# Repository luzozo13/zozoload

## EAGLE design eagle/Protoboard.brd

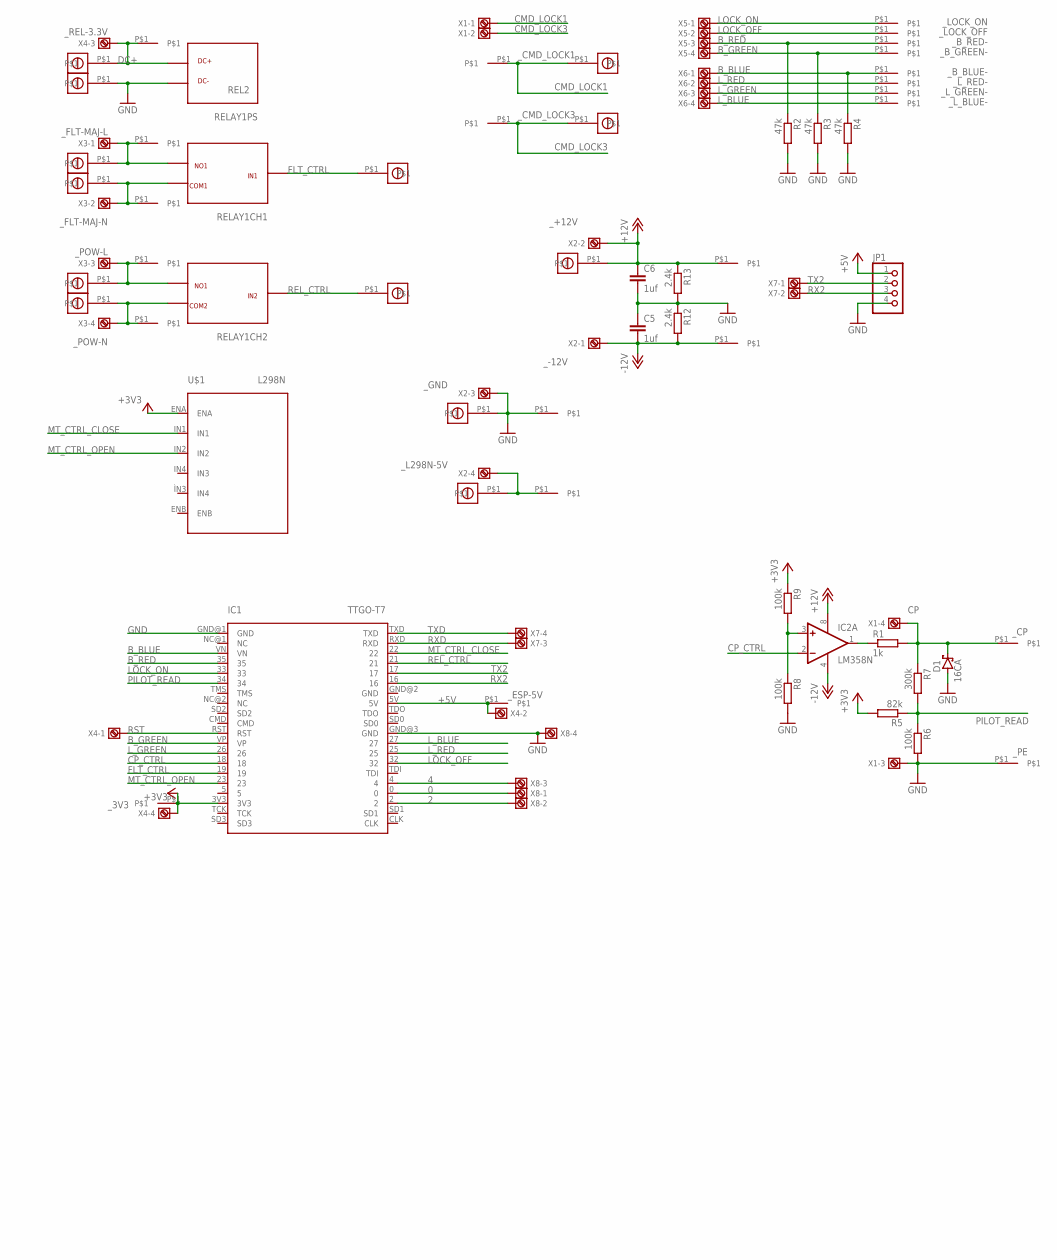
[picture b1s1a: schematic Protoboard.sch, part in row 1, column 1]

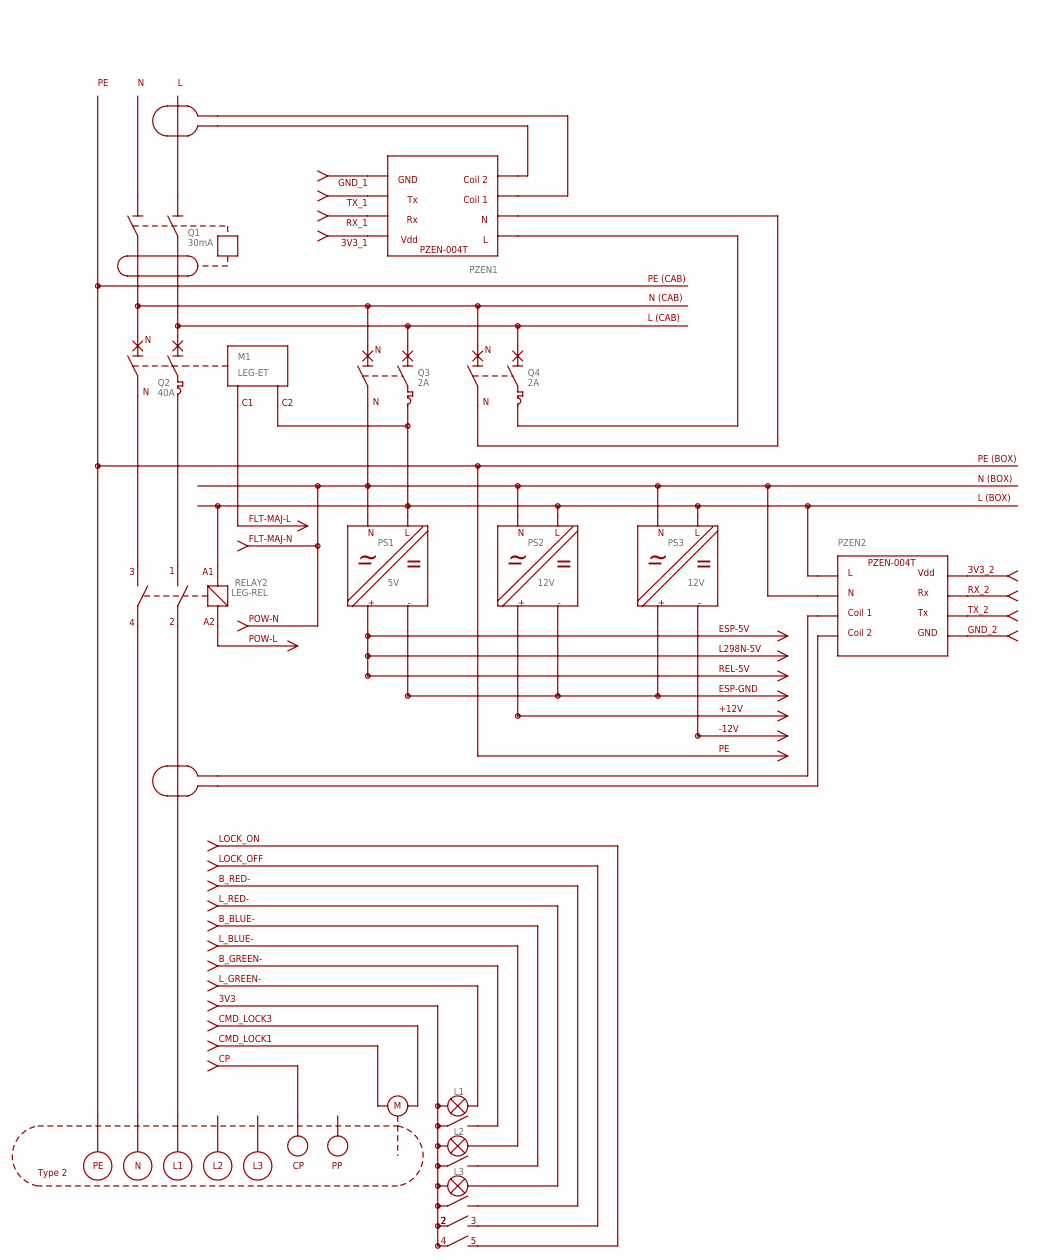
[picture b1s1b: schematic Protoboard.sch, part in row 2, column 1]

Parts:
5V, 12V: BORNIER
C5, C6: 1uf; C050-025X075
D1: 16CA; C1702-15
DC+: BORNIER
DC-: BORNIER
FLT-L: BORNIER
FLT-N: BORNIER
GND: BORNIER
IC1: TTGO-T7
IC2: LM358N; DIL08
IN1, IN2: BORNIER
JP1: PINHD-1X4; 1X04
MT1, MT2: BORNIER
POW-L: BORNIER
POW-N: BORNIER
R1: 1k; 0207/10
R2, R3, R4: 47k; 0207/10
R5: 82k; 0207/10
R6, R8, R9: 100k; 0207/10
R7: 300k; 0207/10
R12, R13: 2.4k; 0207/10
RELAY1: REL2
U$1: L298N
X1, X2, X3, X4, X5, X6, X7, X8: 1727036
_3V3: PIN
_+12V: PIN
_-12V: PIN
_B_BLUE-: PIN
_B_GREEN-: PIN
_B_RED-: PIN
_CMD_LOCK1, _CMD_LOCK3: PIN
_CP: PIN
_ESP-5V: PIN
_FLT-MAJ-L: PIN
_FLT-MAJ-N: PIN
_GND: PIN
_L298N-5V: PIN
_LOCK_OFF: PIN
_LOCK_ON: PIN
_L_BLUE-: PIN
_L_GREEN-: PIN
_L_RED-: PIN
_PE: PIN
_POW-L: PIN
_POW-N: PIN
_REL-3.3V: PIN

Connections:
0: IC1.0, X8.1
2: IC1.2, X8.2
4: IC1.4, X8.3
+3V3: IC1.3V3, R5.2, R9.1, U$1.ENA, X4.4, _3V3.P$1
+5V: IC1.5V, JP1.1, X4.2, _ESP-5V.P$1
+12V: 12V.P$1, C6.1, IC2.8 (V+), R13.1, X2.2, _+12V.P$1
-12V: C5.2, IC2.4 (V-), R12.2, X2.1, _-12V.P$1
B_BLUE: IC1.VN, R4.1, X6.1, _B_BLUE-.P$1
B_GREEN: IC1.VP, R3.1, X5.4, _B_GREEN-.P$1
B_RED: IC1.35, R2.1, X5.3, _B_RED-.P$1
CMD_LOCK1: MT2.P$1, X1.2, _CMD_LOCK1.P$1
CMD_LOCK3: MT1.P$1, X1.1, _CMD_LOCK3.P$1
CP: D1.C, R1.2, R7.1, X1.4, _CP.P$1
CP_CTRL: IC1.18, IC2.2 (-IN)
DC+: DC+.P$1, X4.3, _REL-3.3V.P$1
FLT_CTRL: IC1.19, IN1.P$1
GND: C5.1, C6.2, D1.A, DC-.P$1, GND.P$1, IC1.GND@1 (GND), IC1.GND@3 (GND), JP1.4, R2.2, R3.2, R4.2, R6.2, R8.2, R12.1, R13.2, X1.3, X2.3, X8.4, _GND.P$1, _PE.P$1
LOCK_OFF: IC1.32, X5.2, _LOCK_OFF.P$1
LOCK_ON: IC1.33, X5.1, _LOCK_ON.P$1
L_BLUE: IC1.27, X6.4, _L_BLUE-.P$1
L_GREEN: IC1.26, X6.3, _L_GREEN-.P$1
L_RED: IC1.25, X6.2, _L_RED-.P$1
MT_CTRL_CLOSE: IC1.22, U$1.IN1
MT_CTRL_OPEN: IC1.23, U$1.IN2
unnamed: FLT-N.P$1, X3.2, _FLT-MAJ-N.P$1
unnamed: FLT-L.P$1, X3.1, _FLT-MAJ-L.P$1
unnamed: IC2.1 (OUT), R1.1
unnamed: POW-L.P$1, X3.3, _POW-L.P$1
unnamed: POW-N.P$1, X3.4, _POW-N.P$1
unnamed: IC2.3 (+IN), R8.1, R9.2
unnamed: 5V.P$1, X2.4, _L298N-5V.P$1
PILOT_READ: IC1.34, R5.1, R6.1, R7.2
REL_CTRL: IC1.21, IN2.P$1
RST: IC1.RST, X4.1
RX2: IC1.16, JP1.3, X7.2
RXD: IC1.RXD, X7.3
TX2: IC1.17, JP1.2, X7.1
TXD: IC1.TXD, X7.4

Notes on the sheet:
PE (CAB)
N (CAB)
L (CAB)
PE (BOX)
N (BOX)
L (BOX)
REL-5V
ESP-GND
+12V
-12V
FLT-MAJ-L
FLT-MAJ-N
POW-N
POW-L
CMD_LOCK1
CMD_LOCK3
3V3
L_GREEN-
L_BLUE-
L_RED-
LOCK_OFF
LOCK_ON
L298N-5V
ESP-5V
B_RED-
B_BLUE-
B_GREEN-
GND_2
TX_2
RX_2
3V3_2
GND_1
TX_1
RX_1
3V3_1

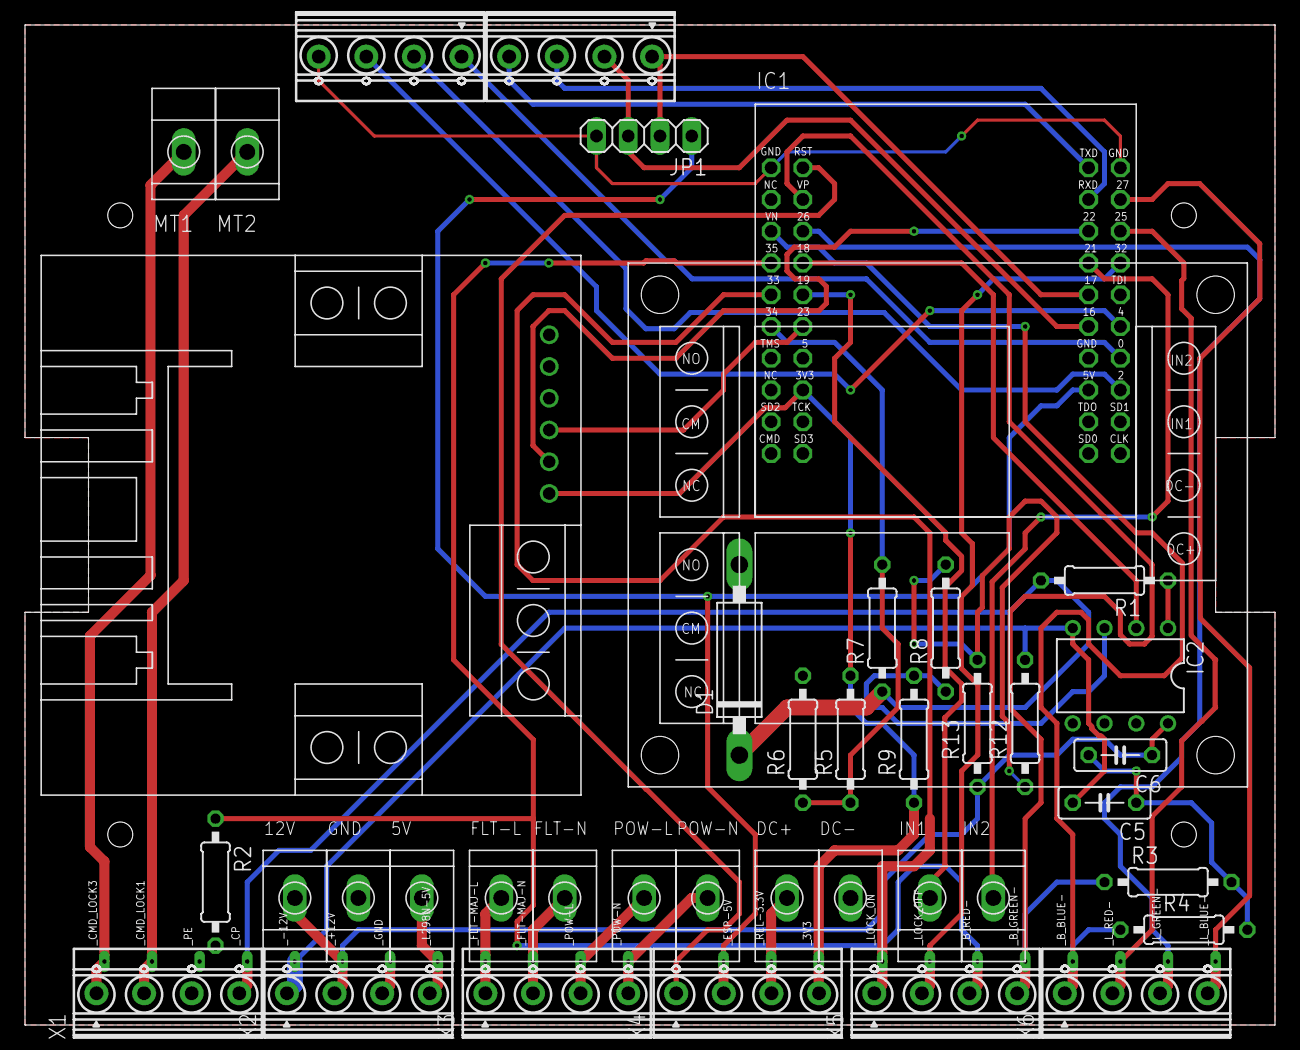
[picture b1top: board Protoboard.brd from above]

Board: 2 copper layers, 100.0 x 80.0 mm, 63 parts (0 on the bottom side), 38 nets.

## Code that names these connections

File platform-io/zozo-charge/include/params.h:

#pragma once

#include <Arduino.h>  // For byte type definition

// Forward declarations
class MqttHandler;
class PZEM004Tv30; // PZEM type forward declaration

//-- Pin Assignments --//
// EV Charger Control Pins
#define CP_CTRL 18          // Control Pilot PWM output
#define FLT_CTRL 19         // Fault control output
#define REL_CTRL 21         // Main relay control
#define MT_CTRL_CLOSE 22    // Motor control - close
#define MT_CTRL_OPEN 23     // Motor control - open

// LED Pins  
#define L_R 25              // Red LED
#define L_G 26              // Green LED
#define L_B 27              // Blue LED

// Lock Control Pins
#define LOCK_ON 32          // Lock engage input
#define LOCK_OFF 33         // Lock disengage input

// Input Pins
#define PILOT_READ 34       // Control Pilot voltage reading (analog)
#define B_R 35              // Red button input
#define B_G 36              // Green button input  
#define B_B 39              // Blue button input

//-- PZEM Current Measurement --//
#define PZEM_RX_PIN 3      // PZEM RX pin (connect to PZEM TX)
#define PZEM_TX_PIN 1      // PZEM TX pin (connect to PZEM RX)
#define PZEM_ADDR 0x04      // PZEM device address
#define PZEM_UPDATE_INTERVAL 5000  // Update every 5 seconds
#define PZEM_TEST_MODE 0    // Set to 1 for simulated readings, 0 for real hardware

//-- PWM Configuration --//
#define CH_CP_CTRL 0        // PWM channel for Control Pilot
#define F_PWM 1000          // PWM frequency in Hz (1kHz)
#define PWM_RES 8           // PWM resolution in bits (8-bit: 0-255)

//-- EVSE State Definitions --//
#define STATE_INIT 0
#define STATE_A 1           // Vehicle not connected
#define STATE_B 2           // Vehicle connected, not ready
#define STATE_C 3           // Vehicle connected and ready/charging
#define STATE_SLEEPING 4    // CP set to +12V, waiting before opening relay (J1772 stop sequence)
#define STATE_FAULT -1      // Fault state

#define SLEEP_RELAY_OPEN_TIMEOUT_MS 3000  // Max ms to wait for EV to release before forcing relay open

//-- CP Fault Detection (state D/E: CP below TH_CD, e.g. CP shorted to ground) --//
// 0 = report only: a steady low CP is published as a "cp_fault_seen" event on
//     state/change, but the state machine ignores it (previous behaviour).
// 1 = enforce: a steady low CP goes to STATE_FAULT (relay open, FLT_CTRL high).
// Run with 0 first and check no event shows up during normal charging.
#define FAULT_DETECT_ENFORCE 0
#define FAULT_RETRY_MS       30000  // Min time held in STATE_FAULT before it may clear

//-- Debug Flags (bitmask — each flag gates its corresponding state topic) --//
#define DBG_DETAILS  0x01   // state/details  (EVSE state periodic)
#define DBG_CHANGE   0x02   // state/change   (EVSE state transitions)
#define DBG_PZEM     0x04   // state/pzem     (power meter telemetry)
#define DBG_COMM     0x08   // state/comm     (connection status)
#define DBG_TIME     0x10   // state/time     (NTP / uptime)

//-- NVS Persistence --//
// Bump NVS_SCHEMA_VERSION to force-reset all NVS settings on next upload
#define NVS_SCHEMA_VERSION  5
#define DBG_DEFAULT_FLAGS   0x1F  // All 5 flags on by default

//-- Power model: car draw vs CP PWM --//
// Measured, linear between POWER_MODEL_PWM_MIN and POWER_MODEL_PWM_MAX:
//   W = POWER_MODEL_W_AT_PWM0 - POWER_MODEL_W_PER_PWM * pwm
// Outside that range the car saturates (its own max current below, its 6A floor
// above). tools/pwm_sweep.py fits these after a sweep and prints the lines to
// paste here (also in the ESPHome port: evse_params.h). Used by set/power_w and
// by the solar jump. Values: sweep of 2026-09-28 (fit over 110-215, worst error
// 178 W); 105 set by hand, where the car stops taking more (7.27 kW, 31 A).
#define POWER_MODEL_W_AT_PWM0  13723.7f  // W, intercept of the fit
#define POWER_MODEL_W_PER_PWM  59.01f    // W less per PWM step
#define POWER_MODEL_PWM_MIN    105       // Most current the car takes (lower PWM: no gain)
#define POWER_MODEL_PWM_MAX    215       // Least current (car's 6A floor)

//-- Solar Tracking Mode --//
// Closed-loop control: every SOLAR_LOOP_MS, compare the energy planner's setpoint
// (MQTT_EVSE_SETPOINT: solar production minus the other loads) vs EVSE
// consumption (PZEM). Outside the deadband, jump straight to the power model's
// PWM for the setpoint (SOLAR_JUMP), or step when the model points the wrong way
// (other car): surplus -> decrement PWM (more current), deficit -> increment PWM
// (less current). PWM clamped to [SOLAR_PWM_MIN, SOLAR_PWM_MAX].
#define SOLAR_JUMP        1     // 0: fixed steps only (no power model)
#define SOLAR_PWM_MIN     POWER_MODEL_PWM_MIN  // Max charging current (lowest PWM duty)
#define SOLAR_PWM_MAX     POWER_MODEL_PWM_MAX  // Min charging current
// Deadband: above the power model's worst error (~210 W) and the setpoint's 10 s
// jitter (p95 ~190 W, 2026-09 HA history), so the loop holds on noise. Each step
// stays below the deadband (x ~59 W/PWM): a step can never overshoot past it.
#define SOLAR_DEADBAND_W  250   // No change when |setpoint - evse_power| <= this
#define SOLAR_STEP_DOWN   3     // PWM decrement step (more current, ~175 W) on surplus
#define SOLAR_STEP_UP     5     // PWM increment step (less current, ~290 W) on deficit
#define SOLAR_LOOP_MS     10000 // Control loop period (ms)
// Setpoint freshness: the energy planner publishes at least every 30 s, and stops
// when the solar meter is silent. With no setpoint message for this long, the loop stops trusting
// the last value and falls back to minimum current (SOLAR_PWM_MAX) until data
// comes back, instead of charging from the grid on a stale surplus.
#define SOLAR_STALE_MS    180000
// Solar pause/resume (anti-flicker): when already at minimum current and still
// in deficit (or setpoint stale), pause charging instead of drawing from the
// grid. Minimum on/off times keep the contactor from cycling on unsteady sun.
#define SOLAR_PAUSE_AFTER_MS   600000   // Deficit at min current this long -> pause
#define SOLAR_MIN_ON_MS        900000   // Never pause sooner than this after charging (re)started
#define SOLAR_MIN_PAUSE_MS    1200000   // Once paused, stay paused at least this long
#define SOLAR_RESUME_W           2300   // Setpoint needed to resume (~8A x 230V + margin)
#define SOLAR_RESUME_AFTER_MS  600000   // Setpoint >= SOLAR_RESUME_W this long -> resume

//-- Unified config NVS defaults --//
#define NVS_DEFAULT_HOSTNAME      "zozo-charge"
#define NVS_DEFAULT_PZEM_ADDR     0x04
#define NVS_DEFAULT_PZEM_ACQ_RATE 5     // seconds
#define NVS_DEFAULT_PZEM_PUB_RATE 30    // seconds (state/pzem publish interval)

//-- Control Pilot Thresholds (ADC values) --//
// Based on J1772 specification voltage levels
#define TH_AB 3770          // Threshold between State A and B (~11V)
#define TH_BC 3135          // Threshold between State B and C (~9V)  
#define TH_CD 2400          // Threshold between State C and D (~6V)

//-- Control Pilot PWM Values --//
// J1772 compliant PWM duty cycles for current encoding
#define CP_AMP_8 221        // 8A charging current
#define CP_AMP_16 187       // 16A charging current
#define CP_AMP_BOOST 170    // Higher current (boost mode)
#define CP_12P 0            // +12V steady state (State A)
#define CP_12N 255          // -12V steady state (fault condition)

//-- Timing Constants --//
// OpenEVSE-style debouncing delays
#define DELAY_STATE_TRANSITION 250    // Standard state transition debounce (ms)
#define DELAY_STATE_TRANSITION_A 25   // Faster debounce for State A (ms)

// Publishing and communication intervals
#define UL_STATE_PUBLISH_INTERVAL 10000  // State publishing interval (ms)
#define MQTT_RECONNECT_INTERVAL   10000  // Min ms between MQTT reconnect attempts (non-blocking)
#define WIFI_CONNECT_TIMEOUT_MS   20000  // Max wait for WiFi in setup(), then continue offline
#define WDT_TIMEOUT_S             10     // Task watchdog: reboot (relay opens) if loop() hangs

// Legacy timing (for compatibility)
#define STATE_CHANGE_DEBOUNCE 10
#define I_DELAY_PILOT_LOOP 12

// Forward declare EVSEController (definition in include/EVSEController.h)
class EVSEController;

// Global EVSE Controller instance
extern EVSEController g_EvseController;
// Global PZEM instance (defined in main.cpp)
extern PZEM004Tv30 pzem;

//-- Function Prototypes --//
// Communication Functions
void reconnect();                     // MQTT reconnection handler

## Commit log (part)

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2024-08-29 Create zozoload.ino
    Initial commit arduino source file
2024-08-29 directory naming requirement
    Change to requirement to have the same directory name as file name
2024-08-29 Eagle first commit
    First commit of all eagle files
2024-08-29 Add libraries to eagle folder
    Add libraries
    Move board project (re-organizing eagle folder)
2024-08-29 Node-red configuration
2025-07-24 Add basic project zozo-charge to migrate from arduino IDE to PlatformIo
2025-07-24 Include templates for wifi and mqtt parameters
2025-07-24 Do not add README to repository
2025-07-24 Draft of the charging scheme
2025-07-27 Add first charging scheme without failure reported from the EV
2025-07-27 Add changing of charging speed via mqqt
2025-07-29 Switch off the LEDs by default
2025-08-18 Tailscale podman script
2025-08-18 Tailscale configuration: Add template for credentials
2025-08-18 Tailscale: Add sudo privileges
2025-08-18 Tailscale: Changes install
2025-09-03 zozocharge: Refactor to a class and implement OpenEVSE logic-like state change.
2025-09-03 zozo-charge: Correct cyclic dependency
2026-01-18 refactor: Complete PZEM integration
    - Add EVSEController.h to version control
    - Harmonize MQTT publishing (voltage, current, power, energy, frequency, power factor)
    - Add frequency and power factor to telemetry
    - Clean up main.cpp code and comments
    - Comprehensive README with examples and troubleshooting
    - Add VS Code settings and tasks for team consistency
2026-05-23 Feature: Add J1772 sleep mode and charge enable/disable control Implement J1772-compliant charging control: CP PWM now gated by charging_enabled flag, with sleep sequence (CP→+12V→3s wait→relay off).
2026-05-24 Enhance MQTT topics with debug flags
2026-05-25 Added solar tracking state to MQTT state details message and added MQTT topic for solar tracking control. Add unified MQTT topics
2026-05-25 Add initial firmware implementation for Sonoff Mini with PZEM-004T integration
2026-05-25 refactor: Update platformio.ini for solar device configuration
